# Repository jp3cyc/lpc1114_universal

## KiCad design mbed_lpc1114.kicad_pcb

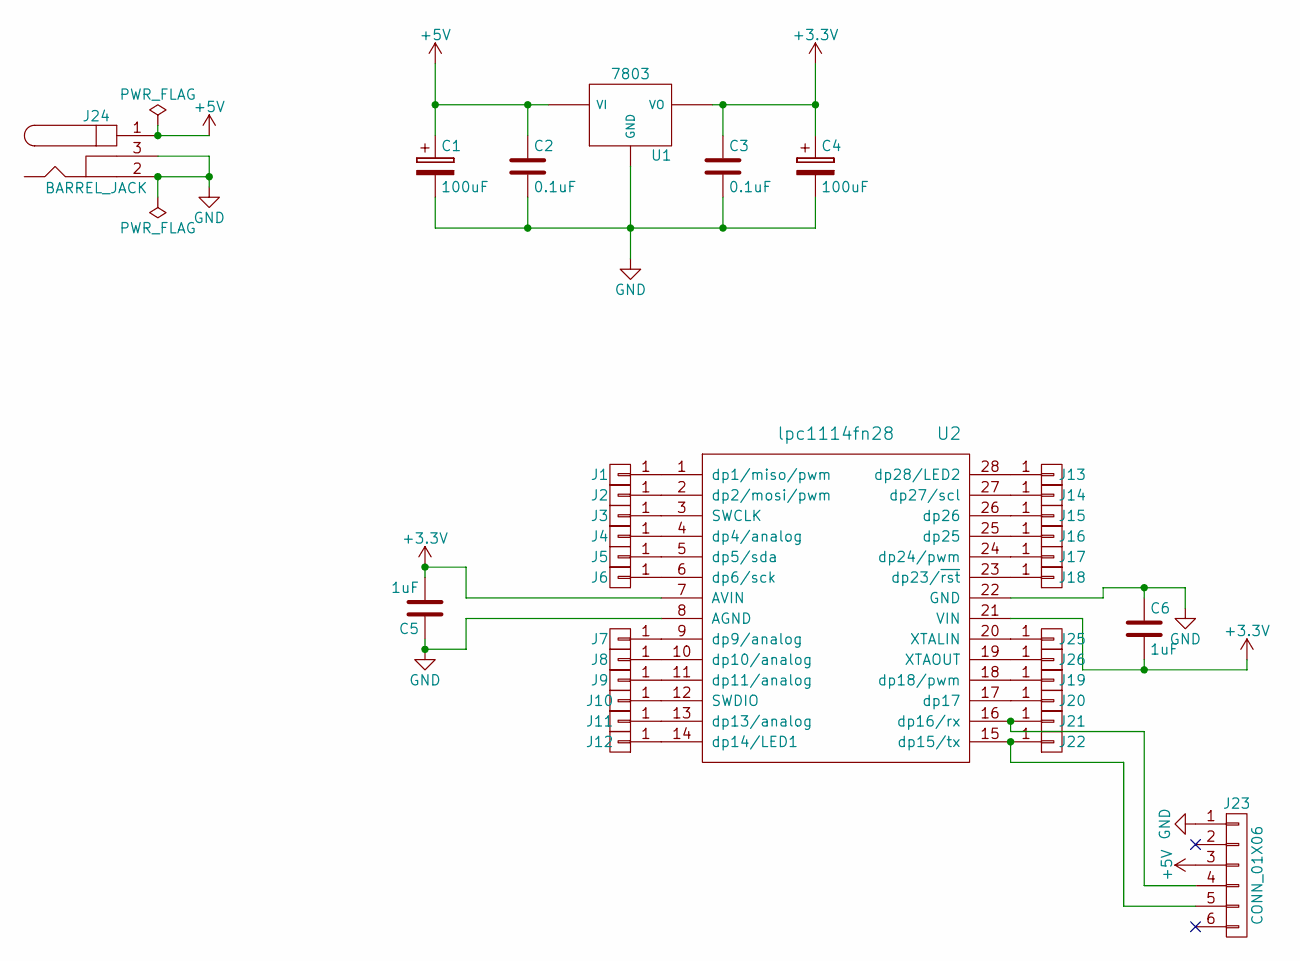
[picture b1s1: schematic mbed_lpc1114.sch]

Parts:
C1, C4: 100uF; CP_Radial_D5.0mm_P2.50mm
C2, C3: 0.1uF; C_0603_HandSoldering
C5, C6: 1uF; C_0603_HandSoldering
J1, J2, J3, J4, J5, J6, J7, J8, J9, J10, J11, J12, J13, J14, J15, J16, J17, J18, J19, J20, J21, J22, J25, J26: CONN_01X01; universal
J23: CONN_01X06; Pin_Header_Straight_1x06_Pitch2.54mm
J24: BARREL_JACK
U1: 7803; TO-252-3_TabPin2
U2: lpc1114fn28; TSSOP-28_4.4x9.7mm_Pitch0.65mm

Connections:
+3V3: C3.1, C4.1, C5.2, C6.2, U1.VO, U2.7 (AVIN), U2.21 (VIN)
+5V: C1.1, C2.1, J23.3, J24.1, U1.VI
GND: C1.2, C2.2, C3.2, C4.2, C5.1, C6.1, J23.1, J24.2, J24.3, U1.GND, U2.8 (AGND), U2.22 (GND)
unnamed: J1.1, U2.1 (dp1/miso/pwm)
unnamed: J2.1, U2.2 (dp2/mosi/pwm)
unnamed: J3.1, U2.3 (SWCLK)
unnamed: J4.1, U2.4 (dp4/analog)
unnamed: J5.1, U2.5 (dp5/sda)
unnamed: J6.1, U2.6 (dp6/sck)
unnamed: J7.1, U2.9 (dp9/analog)
unnamed: J8.1, U2.10 (dp10/analog)
unnamed: J9.1, U2.11 (dp11/analog)
unnamed: J10.1, U2.12 (SWDIO)
unnamed: J11.1, U2.13 (dp13/analog)
unnamed: J12.1, U2.14 (dp14/LED1)
unnamed: J13.1, U2.28 (dp28/LED2)
unnamed: J14.1, U2.27 (dp27/scl)
unnamed: J15.1, U2.26 (dp26)
unnamed: J16.1, U2.25 (dp25)
unnamed: J17.1, U2.24 (dp24/pwm)
unnamed: J18.1, U2.23 (dp23/~rst)
unnamed: J19.1, U2.18 (dp18/pwm)
unnamed: J20.1, U2.17 (dp17)
unnamed: J21.1, J23.4, U2.16 (dp16/rx)
unnamed: J22.1, J23.5, U2.15 (dp15/tx)
unnamed: J25.1, U2.20 (XTALIN)
unnamed: J26.1, U2.19 (XTAOUT)

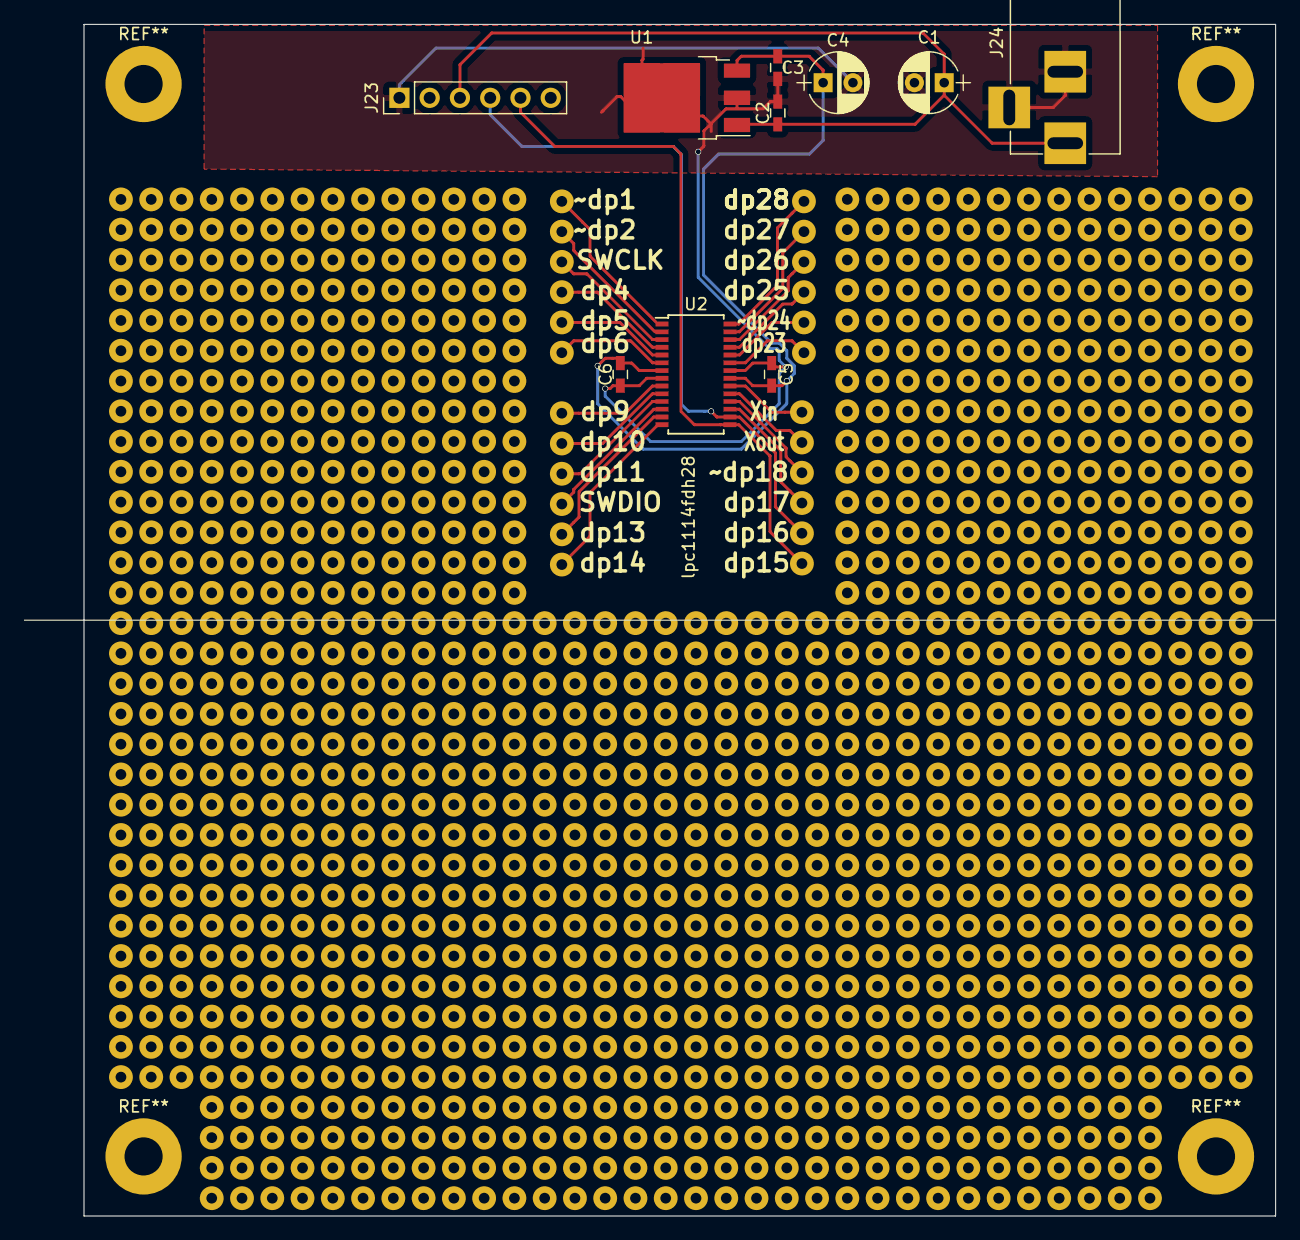
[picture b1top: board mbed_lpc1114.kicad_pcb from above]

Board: 2 copper layers, 105.0 x 100.0 mm, 34 parts (0 on the bottom side), 27 nets.

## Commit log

2017-07-06 :lollipop: Added .gitattributes & .gitignore files
2017-07-06 addProject
2017-07-24 製造ファイル作成
2017-11-25 init
